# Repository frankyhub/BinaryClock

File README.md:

<div align="center">

|[:skull:ISSUE](https://github.com/frankyhub/BinaryClock/issues?q=is%3Aissue)|[:speech_balloon: Forum /Discussion](https://github.com/frankyhub/BinaryClock/discussions)|[:grey_question:WiKi](https://github.com/frankyhub/BinaryClock/wiki)||
|--|--|--|--|
| | | | |
<a href="https://github.com/frankyhub/BinaryClock/issues">|<a href="https://github.com/frankyhub/BinaryClock/discussions">|<a href="https://github.com/frankyhub/BinaryClock/6eleases">||
|| <a href="https://github.com/frankyhub/BinaryClock/pulse" alt="Activity">| <a href="https://github.com/frankyhub/BinaryClock/graphs/traffic">  |<a href="https://github.com/frankyhub?tab=stars"> ||

<br> <br>

<br> <br>

---

<div style="position:absolute; left:2cm; ">   
<ol class="breadcrumb" style="border-top: 2px solid black;border-bottom:2px solid black; height: 45px; width: 900px;"> <p align="center"><a href="#oben">nach oben</a></p></ol>
</div>  

---

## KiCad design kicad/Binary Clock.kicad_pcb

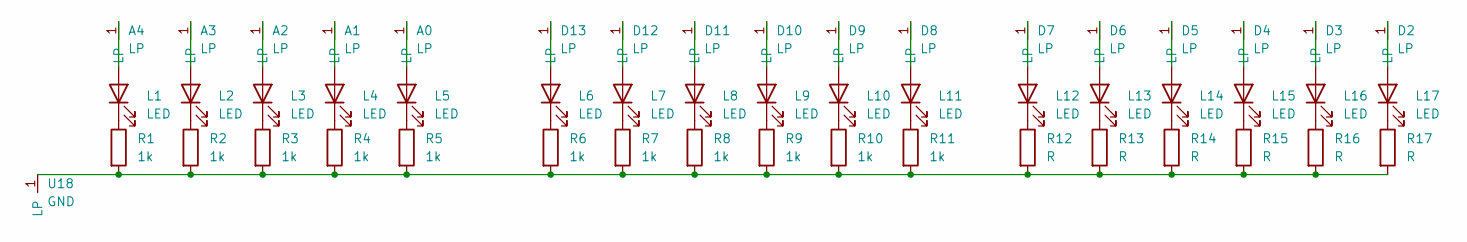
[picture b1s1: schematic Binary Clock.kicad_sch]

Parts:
A0, A1, A2, A3, A4: LP
D2, D3, D4, D5, D7, D8, D9, D10, D11, D12, D13: LP
D6: LP; LP_PCB-Fräse
L1, L2, L3, L4, L5, L6, L7, L8, L9, L10, L11, L12, L13, L14, L15, L16, L17: LED; LED_D5.0mm
R1, R2, R3, R4, R5, R6, R7, R8, R9, R10, R11: 1k; R_Axial_DIN0411_L9.9mm_D3.6mm_P12.70mm_Horizontal
R12, R13, R14, R15, R16, R17: R; R_Axial_DIN0411_L9.9mm_D3.6mm_P12.70mm_Horizontal
U18: GND; LP

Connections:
unnamed: A0.1 (LP), L5.2 (A)
unnamed: A1.1 (LP), L4.2 (A)
unnamed: A2.1 (LP), L3.2 (A)
unnamed: A3.1 (LP), L2.2 (A)
unnamed: A4.1 (LP), L1.2 (A)
unnamed: D2.1 (LP), L17.2 (A)
unnamed: D3.1 (LP), L16.2 (A)
unnamed: D4.1 (LP), L15.2 (A)
unnamed: D5.1 (LP), L14.2 (A)
unnamed: D6.1 (LP), L13.2 (A)
unnamed: D7.1 (LP), L12.2 (A)
unnamed: D8.1 (LP), L11.2 (A)
unnamed: D9.1 (LP), L10.2 (A)
unnamed: D10.1 (LP), L9.2 (A)
unnamed: D11.1 (LP), L8.2 (A)
unnamed: D12.1 (LP), L7.2 (A)
unnamed: D13.1 (LP), L6.2 (A)
unnamed: L1.1 (K), R1.1
unnamed: L2.1 (K), R2.1
unnamed: L3.1 (K), R3.1
unnamed: L4.1 (K), R4.1
unnamed: L5.1 (K), R5.1
unnamed: L6.1 (K), R6.1
unnamed: L7.1 (K), R7.1
unnamed: L8.1 (K), R8.1
unnamed: L9.1 (K), R9.1
unnamed: L10.1 (K), R10.1
unnamed: L11.1 (K), R11.1
unnamed: L12.1 (K), R12.1
unnamed: L13.1 (K), R13.1
unnamed: L14.1 (K), R14.1
unnamed: L15.1 (K), R15.1
unnamed: L16.1 (K), R16.1
unnamed: L17.1 (K), R17.1
unnamed: R1.2, R2.2, R3.2, R4.2, R5.2, R6.2, R7.2, R8.2, R9.2, R10.2, R11.2, R12.2, R13.2, R14.2, R15.2, R16.2, R17.2, U18.1 (LP)

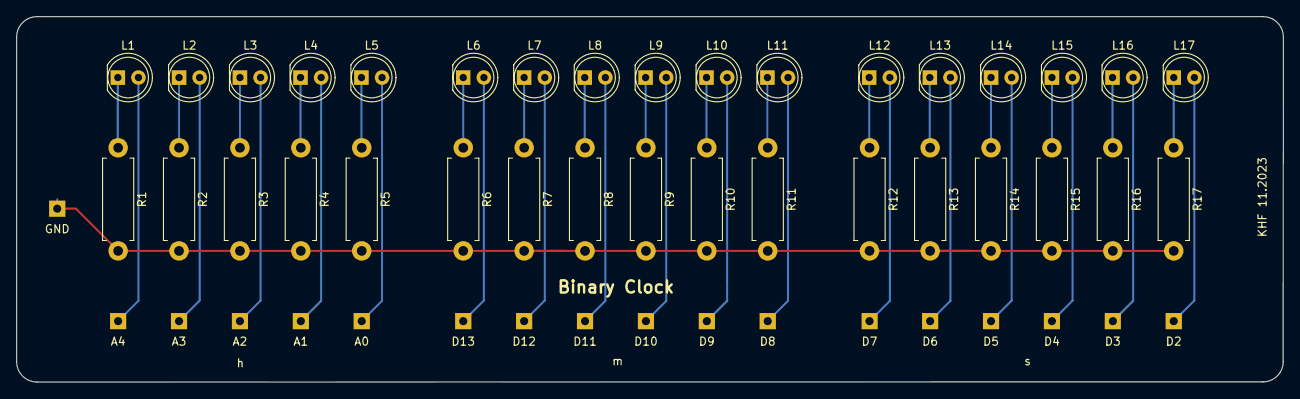
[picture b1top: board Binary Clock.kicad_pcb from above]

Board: 2 copper layers, 156.0 x 45.0 mm, 52 parts (0 on the bottom side), 35 nets.

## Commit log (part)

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2024-06-11 V 11.06.2024
2024-06-13 V13.06.2024
2024-10-12 V12102024
